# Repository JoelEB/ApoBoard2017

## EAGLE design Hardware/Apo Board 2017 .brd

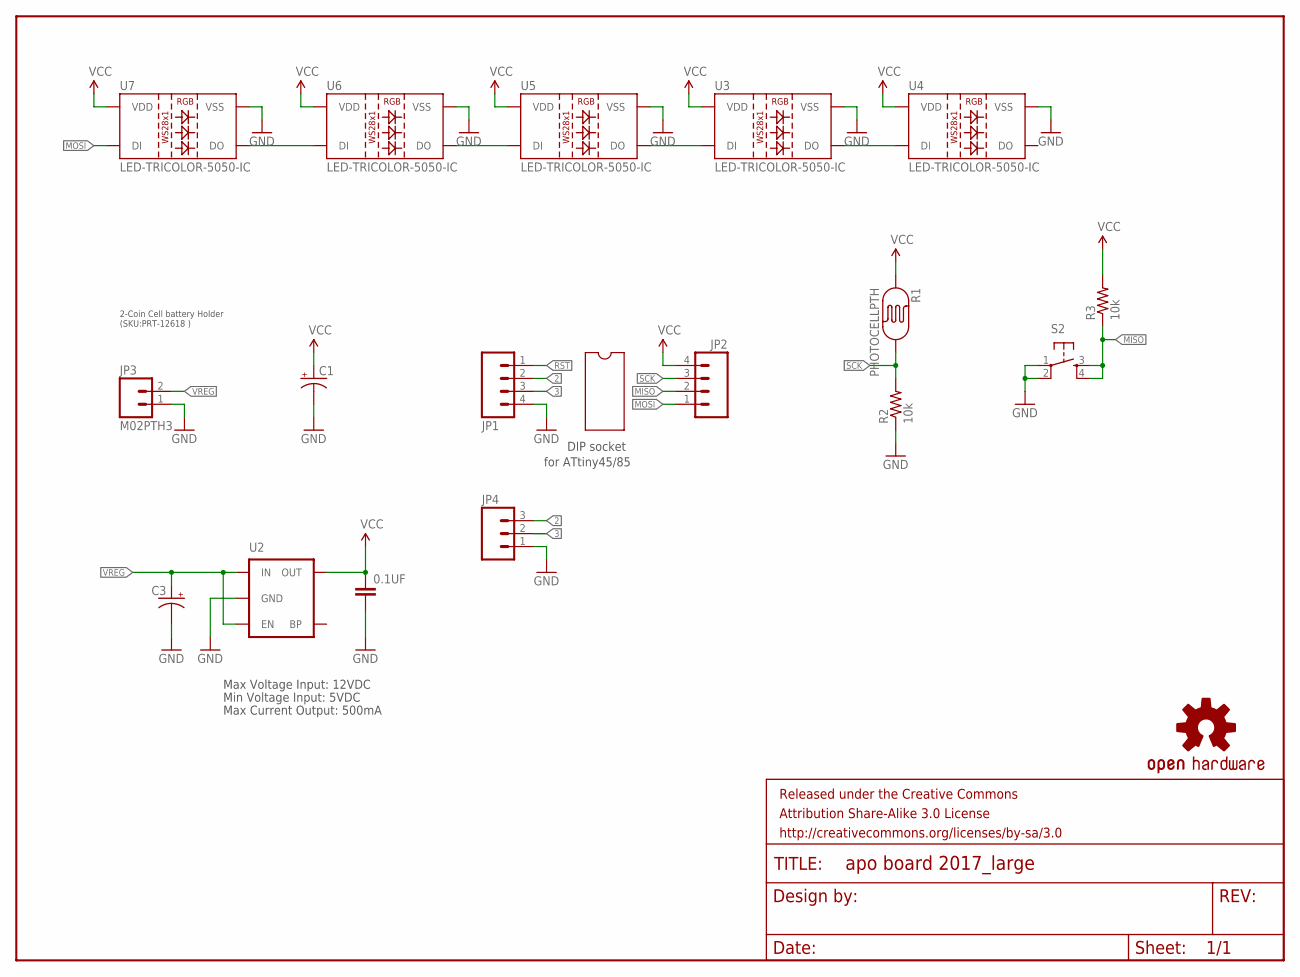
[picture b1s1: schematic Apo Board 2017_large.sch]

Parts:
0.1UF: CAPKIT; CAP-PTH-SMALL-KIT
C1, C3: CAP_POLPTH2; CPOL-RADIAL-10UF-25V
FRAME1: FRAME-LETTER; CREATIVE_COMMONS
JP1, JP2: M04PTH; 1X04
JP3: M02PTH3; 1X02_LONGPADS
JP4: M031X03_NO_SILK; 1X03_NO_SILK
LOGO1: OSHW-LOGOS; OSHW-LOGO-S
R1: PHOTOCELLPTH; PHOTOCELL
R2, R3: 10k; AXIAL-0.4
S2: TAC_SWITCHPTH; TACTILE-PTH
U2: MIC52055V; SOT23-5
U3, U4, U5, U6, U7: LED-TRICOLOR-5050-IC; LED-RGB-THRU

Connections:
2: JP1.2, JP4.3
3: JP1.3, JP4.2
GND: 0.1UF.2, C1.2 (-), C3.2 (-), JP1.4, JP3.1, JP4.1, R2.P$1 (1), S2.1, S2.2, U2.2 (GND), U3.3 (VSS), U4.3 (VSS), U5.3 (VSS), U6.3 (VSS), U7.3 (VSS)
MISO: JP2.2, R3.P$1 (1), S2.3, S2.4
MOSI: JP2.1, U7.1 (DI)
unnamed: U6.1 (DI), U7.4 (DO)
unnamed: U5.1 (DI), U6.4 (DO)
unnamed: U3.1 (DI), U5.4 (DO)
unnamed: U3.4 (DO), U4.1 (DI)
RST: JP1.1
SCK: JP2.3, R1.2, R2.P$2 (2)
VCC: 0.1UF.1, C1.1 (+), JP2.4, R1.1, R3.P$2 (2), U2.5 (OUT), U3.2 (VDD), U4.2 (VDD), U5.2 (VDD), U6.2 (VDD), U7.2 (VDD)
VREG: C3.1 (+), JP3.2, U2.1 (IN), U2.3 (EN)

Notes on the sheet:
DIP socket
for ATtiny45/85
2-Coin Cell battery Holder (SKU:PRT-12618 )
Max Voltage Input: 12VDC
Max Current Output: 500mA
Min Voltage Input: 5VDC

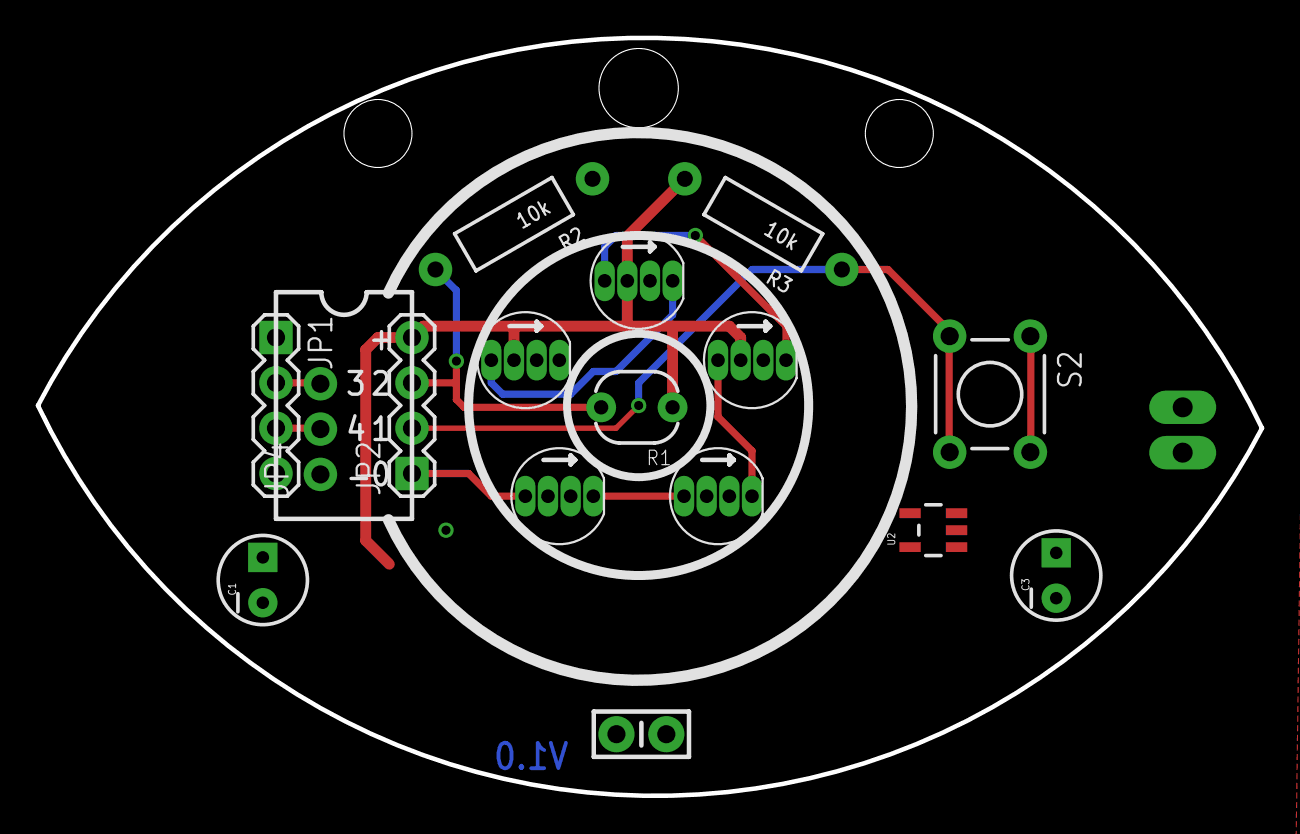
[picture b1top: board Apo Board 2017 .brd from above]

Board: 2 copper layers, 68.6 x 42.5 mm, 19 parts (1 on the bottom side), 12 nets.

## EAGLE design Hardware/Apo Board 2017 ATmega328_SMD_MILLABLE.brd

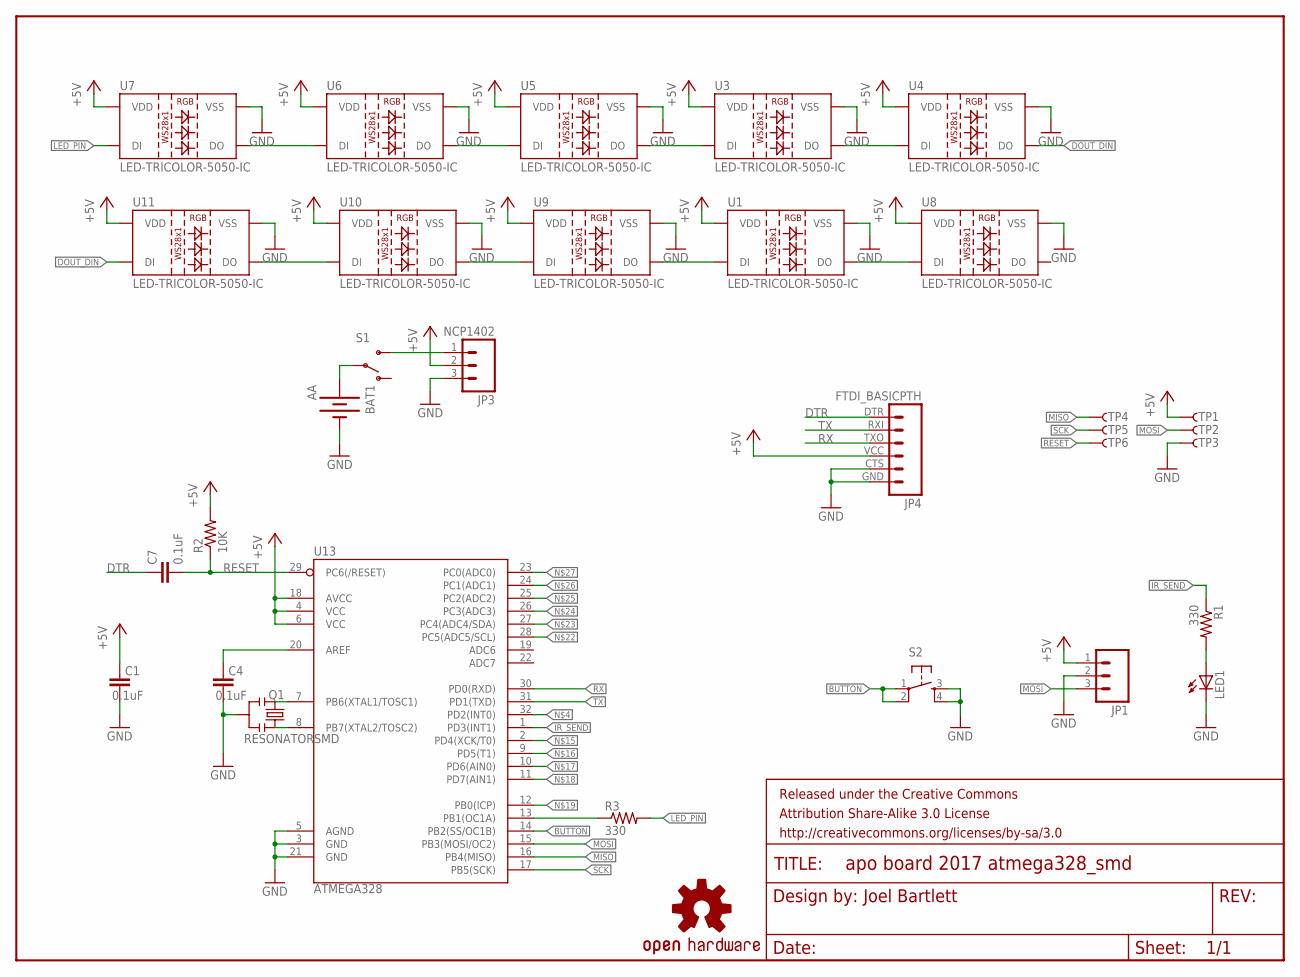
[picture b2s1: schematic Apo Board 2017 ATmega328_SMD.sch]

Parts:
BAT1: AA; BATTERY-AA-KIT
C1, C4, C7: 0.1uF; 0402-CAP
FRAME1: FRAME-LETTER; CREATIVE_COMMONS
JP1: M03IR_RECEIVER; 1X03_IR_RECEIVER
JP3: NCP1402; 1X03_BOOST
JP4: FTDI_BASICPTH; FTDI_BASIC
LED1: LED5MM
LOGO1: OSHW-LOGOS; OSHW-LOGO-S
Q1: RESONATORSMD; RESONATOR-SMD
R1, R3: 330; AXIAL-0.4
R2: 10K; 0402-RES
S1: SWITCH-SPSTKIT; SWITCH-SPDT_KIT
S2: TAC_SWITCHPTH; TACTILE-PTH
TP1, TP2, TP3, TP4, TP5, TP6: TP-3x5; PAD.03X.05
U1, U3, U4, U5, U6, U7, U8, U9, U10, U11: LED-TRICOLOR-5050-IC; LED-RGB-THRU
U13: ATMEGA328; TQFP32-08

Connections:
+5V: C1.2, JP1.1, JP3.2, JP4.VCC (4), R2.2, TP1.P$1, U1.2 (VDD), U3.2 (VDD), U4.2 (VDD), U5.2 (VDD), U6.2 (VDD), U7.2 (VDD), U8.2 (VDD), U9.2 (VDD), U10.2 (VDD), U11.2 (VDD), U13.4 (VCC), U13.6 (VCC), U13.18 (AVCC)
AREF: C4.2, U13.20 (AREF)
BUTTON: S2.1, S2.2, U13.14 (PB2(SS/OC1B))
DOUT_DIN: U4.4 (DO), U11.1 (DI)
DTR: C7.1, JP4.DTR (1)
IR_SEND: R1.P$1 (1), U13.1 (PD3(INT1))
LED_PIN: R3.P$2 (2), U7.1 (DI)
MISO: TP4.P$1, U13.16 (PB4(MISO))
MOSI: JP1.3, TP2.P$1, U13.15 (PB3(MOSI/OC2))
unnamed: U6.1 (DI), U7.4 (DO)
unnamed: U5.1 (DI), U6.4 (DO)
unnamed: LED1.A, R1.P$2 (2)
unnamed: U3.1 (DI), U5.4 (DO)
unnamed: U3.4 (DO), U4.1 (DI)
unnamed: BAT1.PWR@1 (+), S1.2
unnamed: U10.1 (DI), U11.4 (DO)
unnamed: U9.1 (DI), U10.4 (DO)
unnamed: U1.1 (DI), U9.4 (DO)
unnamed: U1.4 (DO), U8.1 (DI)
unnamed: R3.P$1 (1), U13.13 (PB1(OC1A))
unnamed: Q1.1, U13.8 (PB7(XTAL2/TOSC2))
unnamed: Q1.3, U13.7 (PB6(XTAL1/TOSC1))
RESET: C7.2, R2.1, TP6.P$1, U13.29 (PC6(/RESET))
RX: JP4.TXO (3), U13.30 (PD0(RXD))
SCK: TP5.P$1, U13.17 (PB5(SCK))
TX: JP4.RXI (2), U13.31 (PD1(TXD))

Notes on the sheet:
Joel Bartlett

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
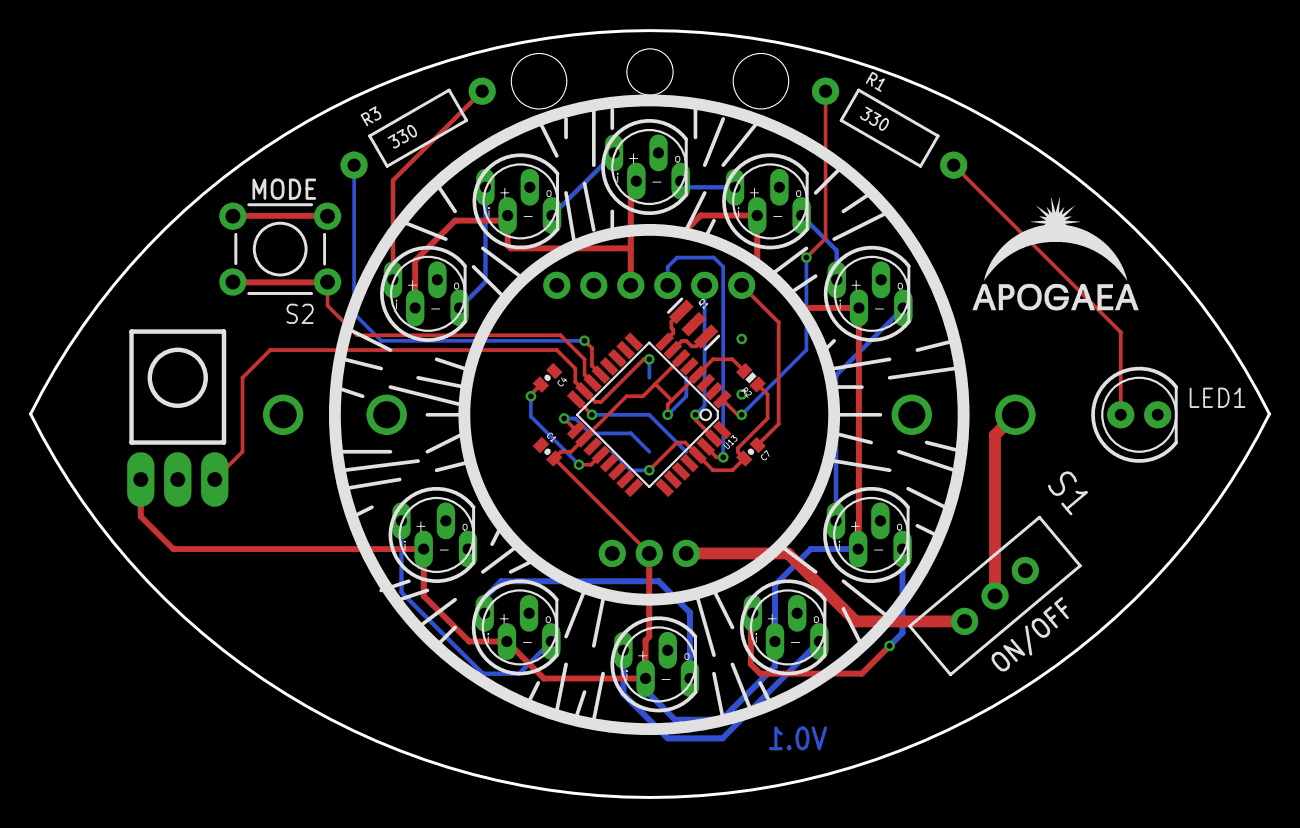
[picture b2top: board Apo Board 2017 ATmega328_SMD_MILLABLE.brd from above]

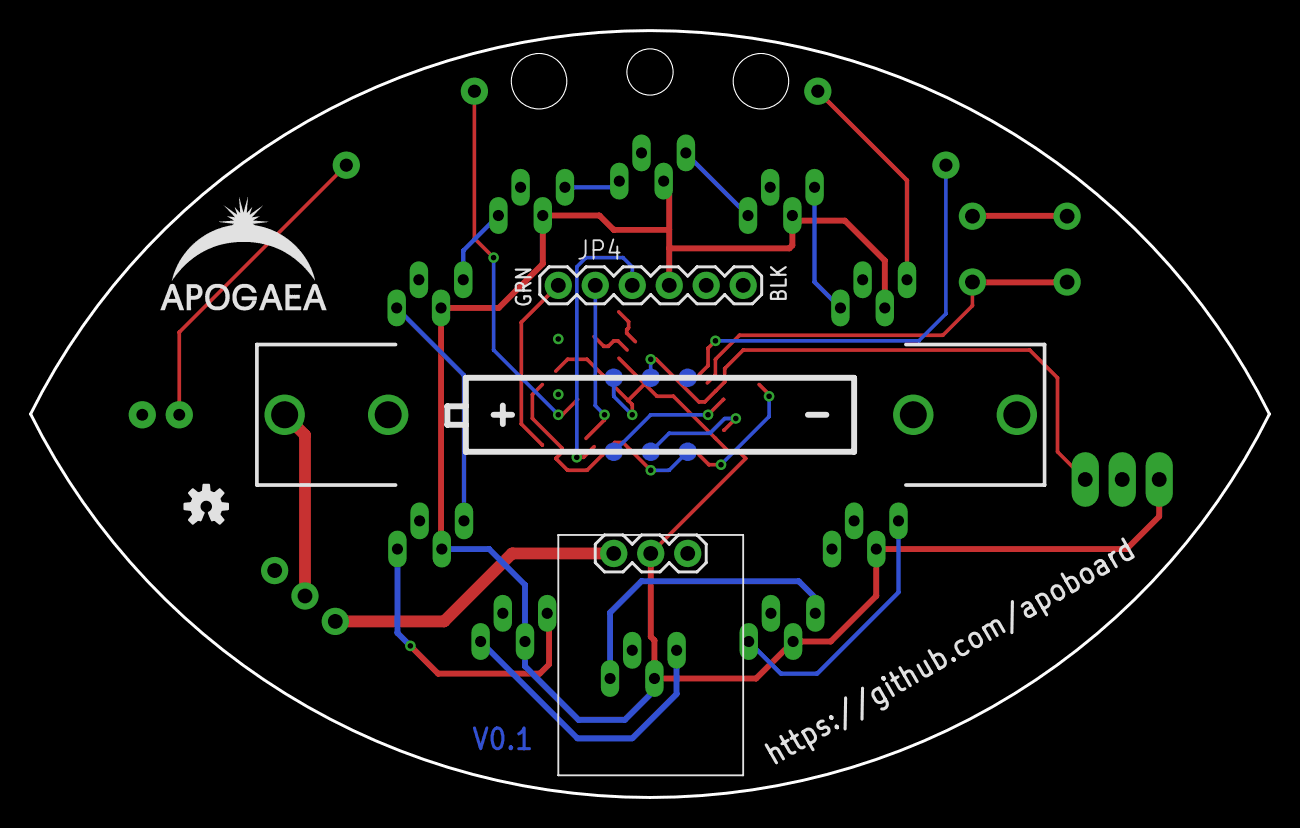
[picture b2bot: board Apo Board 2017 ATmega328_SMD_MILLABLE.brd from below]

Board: 2 copper layers, 85.1 x 52.7 mm, 33 parts (9 on the bottom side), 28 nets.

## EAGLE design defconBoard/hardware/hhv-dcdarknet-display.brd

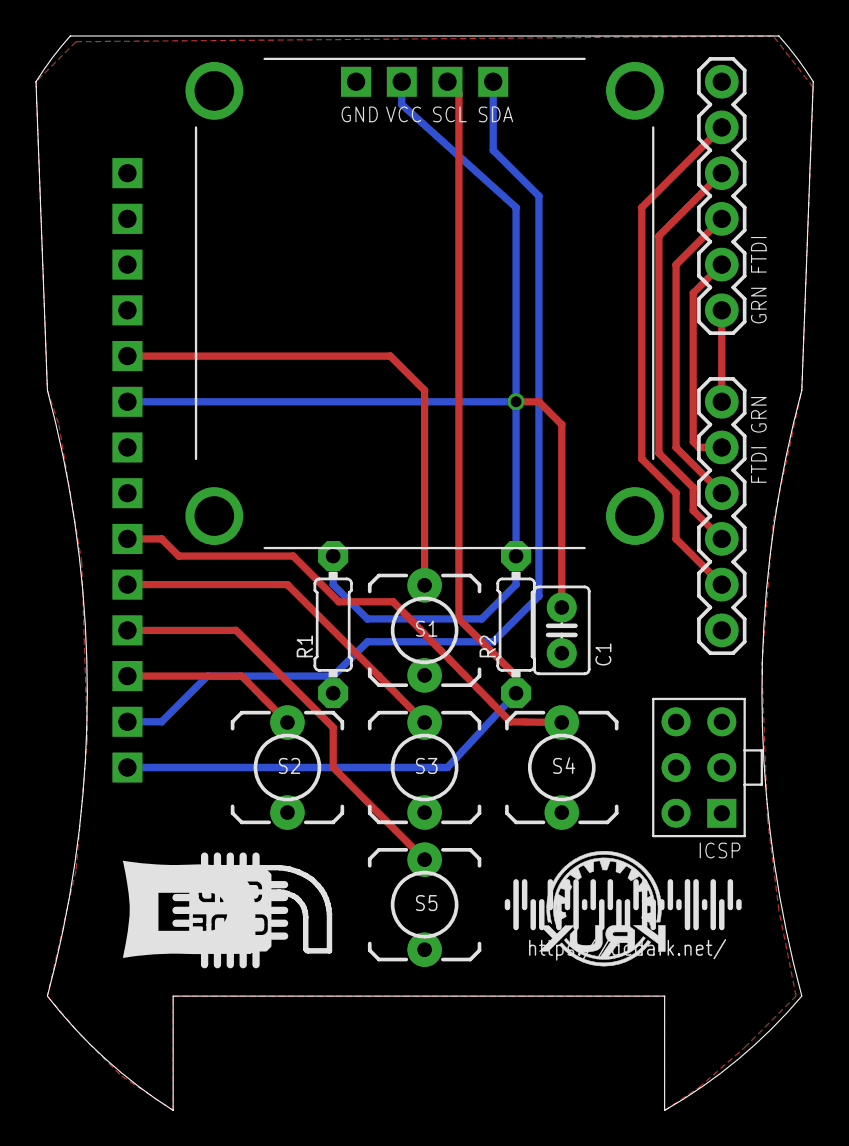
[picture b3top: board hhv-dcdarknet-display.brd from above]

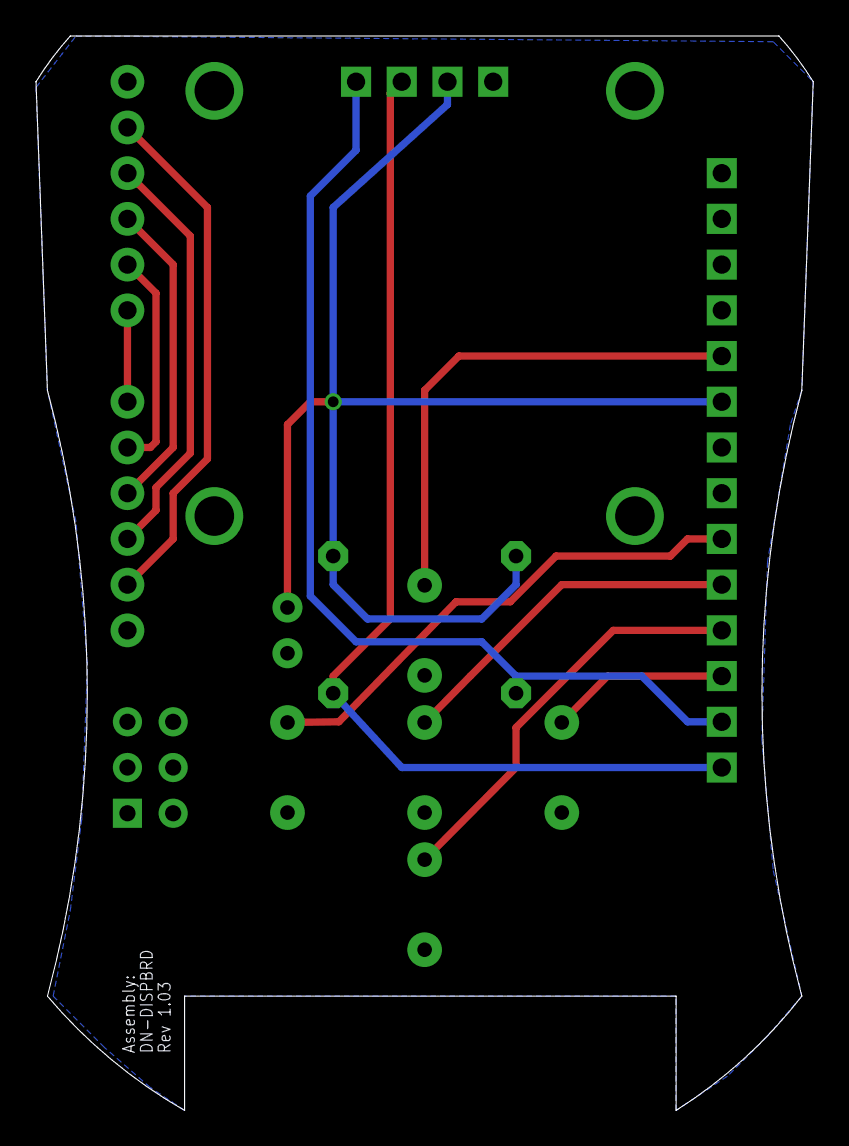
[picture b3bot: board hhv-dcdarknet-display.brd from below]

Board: 2 copper layers, 43.2 x 59.7 mm, 29 parts (2 on the bottom side), 14 nets.

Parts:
C1: .1uF; C025-030X050
JP1: JP1; AVRISP
JP2, JP3: FTDI_BASICPTH; FTDI_BASIC
JP17, JP18, JP19, JP20, JP21, JP22, JP23, JP24, JP25, JP26, JP27, JP28, JP29, JP30: 1X1-SMALL_CUT
R1, R2: 0204/7
S1: UP; TACTILE-2PIN
S2: LEFT; TACTILE-2PIN
S3: CENTER; TACTILE-2PIN
S4: RIGHT; TACTILE-2PIN
S5: DOWN; TACTILE-2PIN
U$1: KRUX_LOGO
U$2: DN_LOGO
U$3: I2C_0.96_OLEDOLED; I2C_0.96_OLED
U$4: CMDC0DE_LOGO; CMDC0DE

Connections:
+3V3: C1.1, JP22.P$1, R1.2, R2.2, U$3.VCC
+5V: JP1.2, JP2.VCC, JP3.VCC
GND: C1.2, JP1.6, JP2.GND, JP3.GND, S1.P$1, S2.P$1, S3.P$1, S4.P$1, S5.P$1, U$3.GND
unnamed: JP2.DTR, JP3.DTR
unnamed: JP2.RXI, JP3.RXI
unnamed: JP2.TXO, JP3.TXO
unnamed: JP2.CTS, JP3.CTS
PIN19: JP21.P$1, S1.P$2
PIN23: JP25.P$1, S4.P$2
PIN24: JP26.P$1, S3.P$2
PIN25: JP27.P$1, S5.P$2
PIN26: JP28.P$1, S2.P$2
PIN27: JP29.P$1, R1.1, U$3.SDA
PIN28: JP30.P$1, R2.1, U$3.SCL

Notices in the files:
parts and their libraries:
SparkFun-Connectors: Licensing: CC v3.0 Share-Alike You are welcome to use this library for commercial purposes.
SparkFun-Aesthetics: Released under the Creative Commons Attribution Share-Alike 3.0 License
SparkFun-Aesthetics: http://creativecommons.org/licenses/by-sa/3.0
